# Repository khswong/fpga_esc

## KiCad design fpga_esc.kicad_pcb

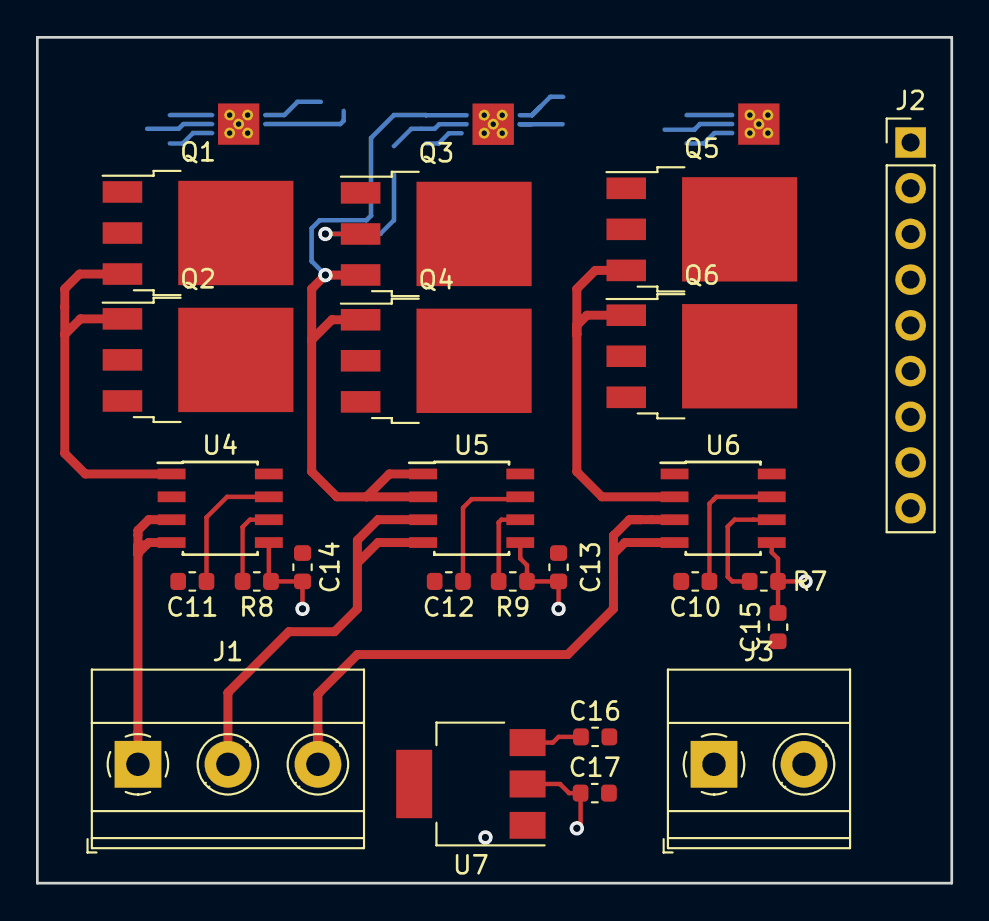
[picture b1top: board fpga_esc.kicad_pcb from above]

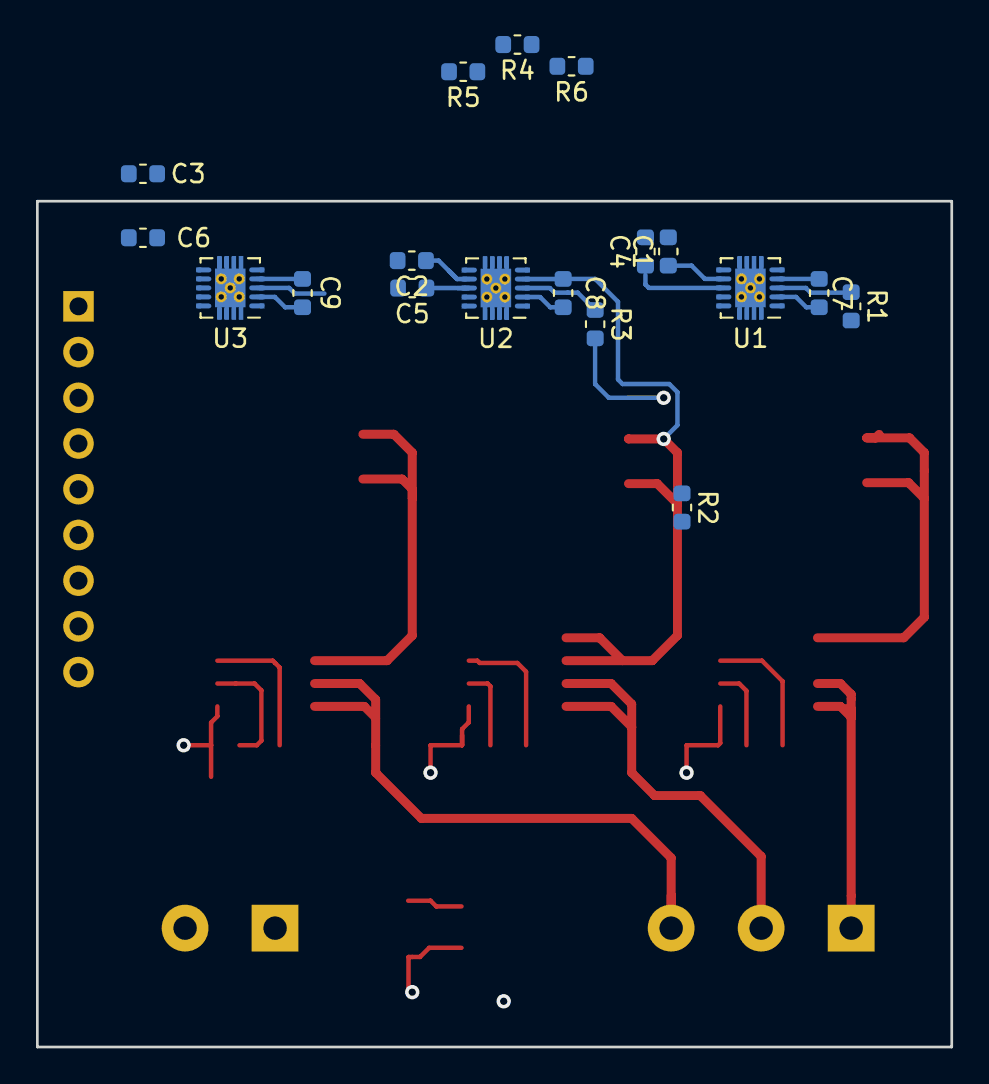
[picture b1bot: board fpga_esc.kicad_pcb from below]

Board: 4 copper layers, 50.8 x 47.0 mm, 42 parts (18 on the bottom side), 36 nets.

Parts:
C1, C2, C3, C4, C5, C6: 100pF; C_0603_1608Metric
C7, C8, C9: 4.7 uF; C_0603_1608Metric
C10, C11, C12: 1nF; C_0603_1608Metric
C13, C14, C15: 0.1uF; C_0603_1608Metric
C16: 100nF; C_0603_1608Metric
C17: 10uF; C_0603_1608Metric
J1: Screw_Terminal_01x03; TerminalBlock_Phoenix_MKDS-1,5-3_1x03_P5.00mm_Horizontal
J2: Conn_01x09_Male; PinHeader_1x09_P2.54mm_Vertical
J3: Screw_Terminal_01x02; TerminalBlock_Phoenix_MKDS-1,5-2_1x02_P5.00mm_Horizontal
Q1, Q2, Q3, Q4, Q5, Q6: IRFR3806TRPBF; TO-252-3_TabPin4
R1, R2, R3, R4, R5, R6: 100R; R_0603_1608Metric
R7, R8, R9: R100; R_0603_1608Metric
U1, U2, U3: UCC27212; Texas_S-PWSON-N10_ThermalVias
U4, U5, U6: ACS711xLCTR-12AB; SOIC-8_3.9x4.9mm_P1.27mm
U7: LD1117S33TR_SOT223; SOT-223-3_TabPin2

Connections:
+3V3: C13.1, C14.1, C15.1, C17.1, R7.1, R8.1, R9.1, U4.5, U5.5, U6.5, U7.2
/Control Signals (from FPGA or microcontroller)/H1: C1.1, J2.9, U1.7
/Control Signals (from FPGA or microcontroller)/H2: C2.1, J2.7, U2.7
/Control Signals (from FPGA or microcontroller)/H3: C3.1, J2.5, U3.7
/Control Signals (from FPGA or microcontroller)/L1: C4.1, J2.8, U1.8
/Control Signals (from FPGA or microcontroller)/L2: C5.1, J2.6, U2.8
/Control Signals (from FPGA or microcontroller)/L3: C6.1, J2.4, U3.8
/Control Signals (from FPGA or microcontroller)/VS_1: C11.1, J2.3, U4.7
/Control Signals (from FPGA or microcontroller)/VS_2: C12.1, J2.2, U5.7
/Control Signals (from FPGA or microcontroller)/VS_3: C10.1, J2.1, U6.7
/Motor Output/fault_1: R8.2, U4.6
/Motor Output/fault_2: R9.2, U5.6
/Motor Output/fault_3: R7.2, U6.6
/Motor Output/output_1: J1.1, U4.3, U4.4
/Motor Output/output_2: J1.2, U5.3, U5.4
/Motor Output/output_3: J1.3, U6.3, U6.4
/Three Phase Bridge/PHASE_1: C7.2, Q1.3, Q2.1, U1.4, U4.1, U4.2
/Three Phase Bridge/PHASE_2: C8.2, Q3.3, Q4.1, U2.4, U5.1, U5.2
/Three Phase Bridge/PHASE_3: C9.2, Q5.3, Q6.1, U3.4, U6.1, U6.2
GND: C1.2, C2.2, C3.2, C4.2, C5.2, C6.2, C10.2, C11.2, C12.2, C13.2, C14.2, C15.2, C16.2, C17.2, J3.2, Q2.3, Q4.3, Q6.3, U1.9, U1.11, U2.9, U2.11, U3.9, U3.11, U4.8, U5.8, U6.8, U7.1
unnamed: C7.1, U1.2
unnamed: C8.1, U2.2
unnamed: C9.1, U3.2
unnamed: Q1.2, R1.2
unnamed: Q2.2, R2.2
unnamed: Q3.2, R3.2
unnamed: Q4.2, R4.2
unnamed: Q5.2, R5.2
unnamed: Q6.2, R6.2
unnamed: R1.1, U1.3
unnamed: R2.1, U1.10
unnamed: R3.1, U2.3
unnamed: R4.1, U2.10
unnamed: R5.1, U3.3
unnamed: R6.1, U3.10
V_POWER: C16.1, J3.1, Q1.1, Q3.1, Q5.1, U1.1, U2.1, U3.1, U7.3

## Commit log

2021-02-09 Smaller form-factor
